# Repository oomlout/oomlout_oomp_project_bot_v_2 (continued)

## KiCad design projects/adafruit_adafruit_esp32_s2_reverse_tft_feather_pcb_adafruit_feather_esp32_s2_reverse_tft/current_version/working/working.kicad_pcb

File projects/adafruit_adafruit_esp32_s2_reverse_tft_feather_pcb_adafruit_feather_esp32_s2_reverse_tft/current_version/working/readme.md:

# adafruit_esp32_s2_reverse_tft_feather_pcb
 
## summary 
* id: adafruit_adafruit_esp32_s2_reverse_tft_feather_pcb_adafruit_feather_esp32_s2_reverse_tft
* user: adafruit
* name: adafruit_esp32_s2_reverse_tft_feather_pcb
* board: adafruit_feather_esp32_s2_reverse_tft
* repo: https://github.com/adafruit/Adafruit-ESP32-S2-Reverse-TFT-Feather-PCB

* src_file_repo_sch: 
* src_file_repo_sch_link: https://github.com/adafruit/Adafruit-ESP32-S2-Reverse-TFT-Feather-PCB/tree/main/
* full details link: https://github.com/oomlout/oomlout_oomp_project_bot_v_2/tree/main/projects/adafruit_adafruit_esp32_s2_reverse_tft_feather_pcb_adafruit_feather_esp32_s2_reverse_tft/current_version/working  

## schematic  
  
[schematic (pdf)](working_schematic.pdf) 

## pcb  

[board (pdf)](working.pdf)  

## working_bom
| Id | Designator | Footprint | Quantity | Designation | Supplier and ref |  | None | 
| --- | --- | --- | --- | --- | --- | --- | --- | 
| 1 | PLABEL17 | PLABEL17 | 1 |  |  |  | [''] | 
| 2 | R10,R4,R8,R2,R5 | 0603-NO | 5 | 5.1K |  |  | [''] | 
| 3 | C4,C5,C10,C11 | 0603-NO | 4 | 1uF |  |  | [''] | 
| 4 | C6,C8,C9,C1,C7,C3,C12,C2 | 0805-NO | 8 | 10uF |  |  | [''] | 
| 5 | PLABEL12 | PLABEL12 | 1 |  |  |  | [''] | 
| 6 | PLABEL16 | PLABEL16 | 1 |  |  |  | [''] | 
| 7 | PLABEL9 | PLABEL9 | 1 |  |  |  | [''] | 
| 8 | PLABEL0 | PLABEL0 | 1 |  |  |  | [''] | 
| 9 | PLABEL20 | PLABEL20 | 1 |  |  |  | [''] | 
| 10 | X2 | TDFN8_2X2MM | 1 | MAX17048/T |  |  | [''] | 
| 11 | PLABEL24 | PLABEL24 | 1 |  |  |  | [''] | 
| 12 | PLABEL15 | PLABEL15 | 1 |  |  |  | [''] | 
| 13 | U$35,U$34 | FIDUCIAL_1MM | 2 | FIDUCIAL_1MM |  |  | [''] | 
| 14 | PLABEL21 | PLABEL21 | 1 |  |  |  | [''] | 
| 15 | R17 | 0603-NO | 1 | 1Meg |  |  | [''] | 
| 16 | R13 | RESPACK_4X0603 | 1 | 10K Pack |  |  | [''] | 
| 17 | PLABEL28 | PLABEL28 | 1 |  |  |  | [''] | 
| 18 | PLABEL5 | PLABEL5 | 1 |  |  |  | [''] | 
| 19 | PLABEL1 | PLABEL1 | 1 |  |  |  | [''] | 
| 20 | U4 | BME280 | 1 | BME280 |  |  | [''] | 
| 21 | @HOLE1,@HOLE0 |  | 2 |  |  |  | [''] | 
| 22 | PLABEL18 | PLABEL18 | 1 |  |  |  | [''] | 
| 23 | PLABEL25 | PLABEL25 | 1 |  |  |  | [''] | 
| 24 | PLABEL6 | PLABEL6 | 1 |  |  |  | [''] | 
| 25 | U5,U2 | SOT23-5 | 2 | RT9080/AP2112-3.3 |  |  | [''] | 
| 26 | PLABEL14 | PLABEL14 | 1 |  |  |  | [''] | 
| 27 | X1 | JSTPH2_BATT | 1 | JSTPH |  |  | [''] | 
| 28 | D3 | CHIPLED_0603_NOOUTLINE | 1 | RED |  |  | [''] | 
| 29 | JP1 | 1X16_ROUND_MIN | 1 |  |  |  | [''] | 
| 30 | CHG0 | CHIPLED_0603_NOOUTLINE | 1 | ORANGE |  |  | [''] | 
| 31 | PLABEL2 | PLABEL2 | 1 |  |  |  | [''] | 
| 32 | Q3 | SOT23-R | 1 | DMG3415U |  |  | [''] | 
| 33 | PLABEL4 | PLABEL4 | 1 |  |  |  | [''] | 
| 34 | PLABEL13 | PLABEL13 | 1 |  |  |  | [''] | 
| 35 | PLABEL31 | PLABEL31 | 1 |  |  |  | [''] | 
| 36 | U3 | SOT23-5 | 1 | MCP73831T-2ACI/OT |  |  | [''] | 
| 37 | R9 | 0603-NO | 1 | 22ohm |  |  | [''] | 
| 38 | PLABEL30 | PLABEL30 | 1 |  |  |  | [''] | 
| 39 | D4 | SOD-123 | 1 | MBR540 |  |  | [''] | 
| 40 | PLABEL19 | PLABEL19 | 1 |  |  |  | [''] | 
| 41 | PLABEL27 | PLABEL27 | 1 |  |  |  | [''] | 
| 42 | PLABEL8 | PLABEL8 | 1 |  |  |  | [''] | 
| 43 | JP3 | 1X12_ROUND_MIN | 1 |  |  |  | [''] | 
| 44 | Q1 | SC70 | 1 | BSS138 |  |  | [''] | 
| 45 | X3 | USB_C_CUSB31-CFM2AX-01-X | 1 | USB C |  |  | [''] | 
| 46 | R1 | 0603-NO | 1 | 10K |  |  | [''] | 
| 47 | SW2,SW5,SW3,SW1,SW4 | BTN_RKB2_4.6X2.8 | 5 | KMR2 |  |  | [''] | 
| 48 | R12,R7 | 0603-NO | 2 | 100K |  |  | [''] | 
| 49 | PLABEL11 | PLABEL11 | 1 |  |  |  | [''] | 
| 50 | PLABEL26 | PLABEL26 | 1 |  |  |  | [''] | 
| 51 | PLABEL29 | PLABEL29 | 1 |  |  |  | [''] | 
| 52 | PLABEL3 | PLABEL3 | 1 |  |  |  | [''] | 
| 53 | PLABEL7 | PLABEL7 | 1 |  |  |  | [''] | 
| 54 | PLABEL22 | PLABEL22 | 1 |  |  |  | [''] | 
| 55 | U$32,U$31 | MOUNTINGHOLE_2.5_PLATED | 2 | MOUNTINGHOLE2.5 |  |  | [''] | 
| 56 | LED1 | SK6805_1515 | 1 | WS2812B_SK6805_1515 |  |  | [''] | 
| 57 | CONN1 | JST_SH4_RA | 1 | STEMMA_I2C_QTRA |  |  | [''] | 
| 58 | PLABEL23 | PLABEL23 | 1 |  |  |  | [''] | 
| 59 | PLABEL10 | PLABEL10 | 1 |  |  |  | [''] | 
| 60 | U1 | ESP32-S2-MINI-1 | 1 | ESP32-S2-MODULE_MINI |  |  | [''] | 
| 61 | PLABEL32 | PLABEL32 | 1 |  |  |  | [''] | 
| 62 | PLABEL33 | PLABEL33 | 1 |  |  |  | [''] | 
| 63 | PLABEL35 | PLABEL35 | 1 |  |  |  | [''] | 
| 64 | PLABEL34 | PLABEL34 | 1 |  |  |  | [''] | 
| 65 | PLABEL36 | PLABEL36 | 1 |  |  |  | [''] | 
| 66 | DISP1 | TFT_1.14IN_240X135_WRAPUNDER | 1 | DISP_LCD_GENERIC_SPI_1.14IN_240X135_WRAPUNDER |  |  | [''] | 
| 67 | TP1 | TESTPOINT_ROUND_1.5MM_NO | 1 |  |  |  | [''] | 

## bom_schematic
| Ref | Qnty | Value | Cmp name | Footprint | Description | Vendor | DNP | 
| --- | --- | --- | --- | --- | --- | --- | --- | 
| C1, C2, C3, C6, C7, C8, C9, C12 | 8 | 10uF | CAP_CERAMIC0805-NOOUTLINE | working:0805-NO |  |  |  | 
| C4, C5, C10, C11 | 4 | 1uF | CAP_CERAMIC0603_NO | working:0603-NO |  |  |  | 
| CHG0 | 1 | ORANGE | LED0603_NOOUTLINE | working:CHIPLED_0603_NOOUTLINE |  |  |  | 
| CONN1 | 1 | STEMMA_I2C_QTRA | STEMMA_I2C_QTRA | working:JST_SH4_RA |  |  |  | 
| D3 | 1 | RED | LED0603_NOOUTLINE | working:CHIPLED_0603_NOOUTLINE |  |  |  | 
| D4 | 1 | MBR540 | DIODE-SCHOTTKYSOD-123 | working:SOD-123 |  |  |  | 
| DISP1 | 1 | DISP_LCD_GENERIC_SPI_1.14IN_240X135_WRAPUNDER | DISP_LCD_GENERIC_SPI_1.14IN_240X135_WRAPUNDER | working:TFT_1.14IN_240X135_WRAPUNDER |  |  |  | 
| JP1 | 1 | HEADER-1X16_MIN | HEADER-1X16_MIN | working:1X16_ROUND_MIN |  |  |  | 
| JP3 | 1 | HEADER-1X12_MIN | HEADER-1X12_MIN | working:1X12_ROUND_MIN |  |  |  | 
| LED1 | 1 | WS2812B_SK6805_1515 | WS2812B_SK6805_1515 | working:SK6805_1515 |  |  |  | 
| Q1 | 1 | BSS138 | MOSFET-N_SC70 | working:SC70 |  |  |  | 
| Q3 | 1 | DMG3415U | MOSFET-P | working:SOT23-R |  |  |  | 
| R1 | 1 | 10K | RESISTOR_0603_NOOUT | working:0603-NO |  |  |  | 
| R2, R4, R5, R8, R10 | 5 | 5.1K | RESISTOR_0603_NOOUT | working:0603-NO |  |  |  | 
| R7, R12 | 2 | 100K | RESISTOR_0603_NOOUT | working:0603-NO |  |  |  | 
| R9 | 1 | 22ohm | RESISTOR_0603_NOOUT | working:0603-NO |  |  |  | 
| R13 | 1 | 10K Pack | RESISTOR_4PACK | working:RESPACK_4X0603 |  |  |  | 
| R17 | 1 | 1Meg | RESISTOR_0603_NOOUT | working:0603-NO |  |  |  | 
| SW1, SW2, SW3, SW4, SW5 | 5 | KMR2 | SWITCH_TACT_SMT_RKB2 | working:BTN_RKB2_4.6X2.8 |  |  |  | 
| TP1 | 1 | TESTPOINTROUND1.5MMNO | TESTPOINTROUND1.5MMNO | working:TESTPOINT_ROUND_1.5MM_NO |  |  |  | 
| U1 | 1 | ESP32-S2-MODULE_MINI | ESP32-S2-MODULE_MINI | working:ESP32-S2-MINI-1 |  |  |  | 
| U2, U5 | 2 | RT9080/AP2112-3.3 | VREG_SOT23-5 | working:SOT23-5 |  |  |  | 
| U3 | 1 | MCP73831T-2ACI/OT | MCP73831/2 | working:SOT23-5 |  |  |  | 
| U4 | 1 | BME280 | BME280 | working:BME280 |  |  |  | 
| U$31, U$32 | 2 | MOUNTINGHOLE2.5 | MOUNTINGHOLE2.5 | working:MOUNTINGHOLE_2.5_PLATED |  |  |  | 
| U$34, U$35 | 2 | FIDUCIAL_1MM | FIDUCIAL_1MM | working:FIDUCIAL_1MM |  |  |  | 
| X1 | 1 | CON_JST_PH_2PIN_MT_BATT | CON_JST_PH_2PIN_MT_BATT | working:JSTPH2_BATT |  |  |  | 
| X2 | 1 | MAX17048/T | MAX17048/T | working:TDFN8_2X2MM |  |  |  | 
| X3 | 1 | USB C | USB_C | working:USB_C_CUSB31-CFM2AX-01-X |  |  |  | 

## mounting_holes
| x | y | package | value | ref | size | 
| --- | --- | --- | --- | --- | --- | 
| 0.0 | 17.78 | MOUNTINGHOLE_2.5_PLATED | MOUNTINGHOLE2.5 | U$31 | m3 | 
| 0.0 | 0.0 | MOUNTINGHOLE_2.5_PLATED | MOUNTINGHOLE2.5 | U$32 | m3 |

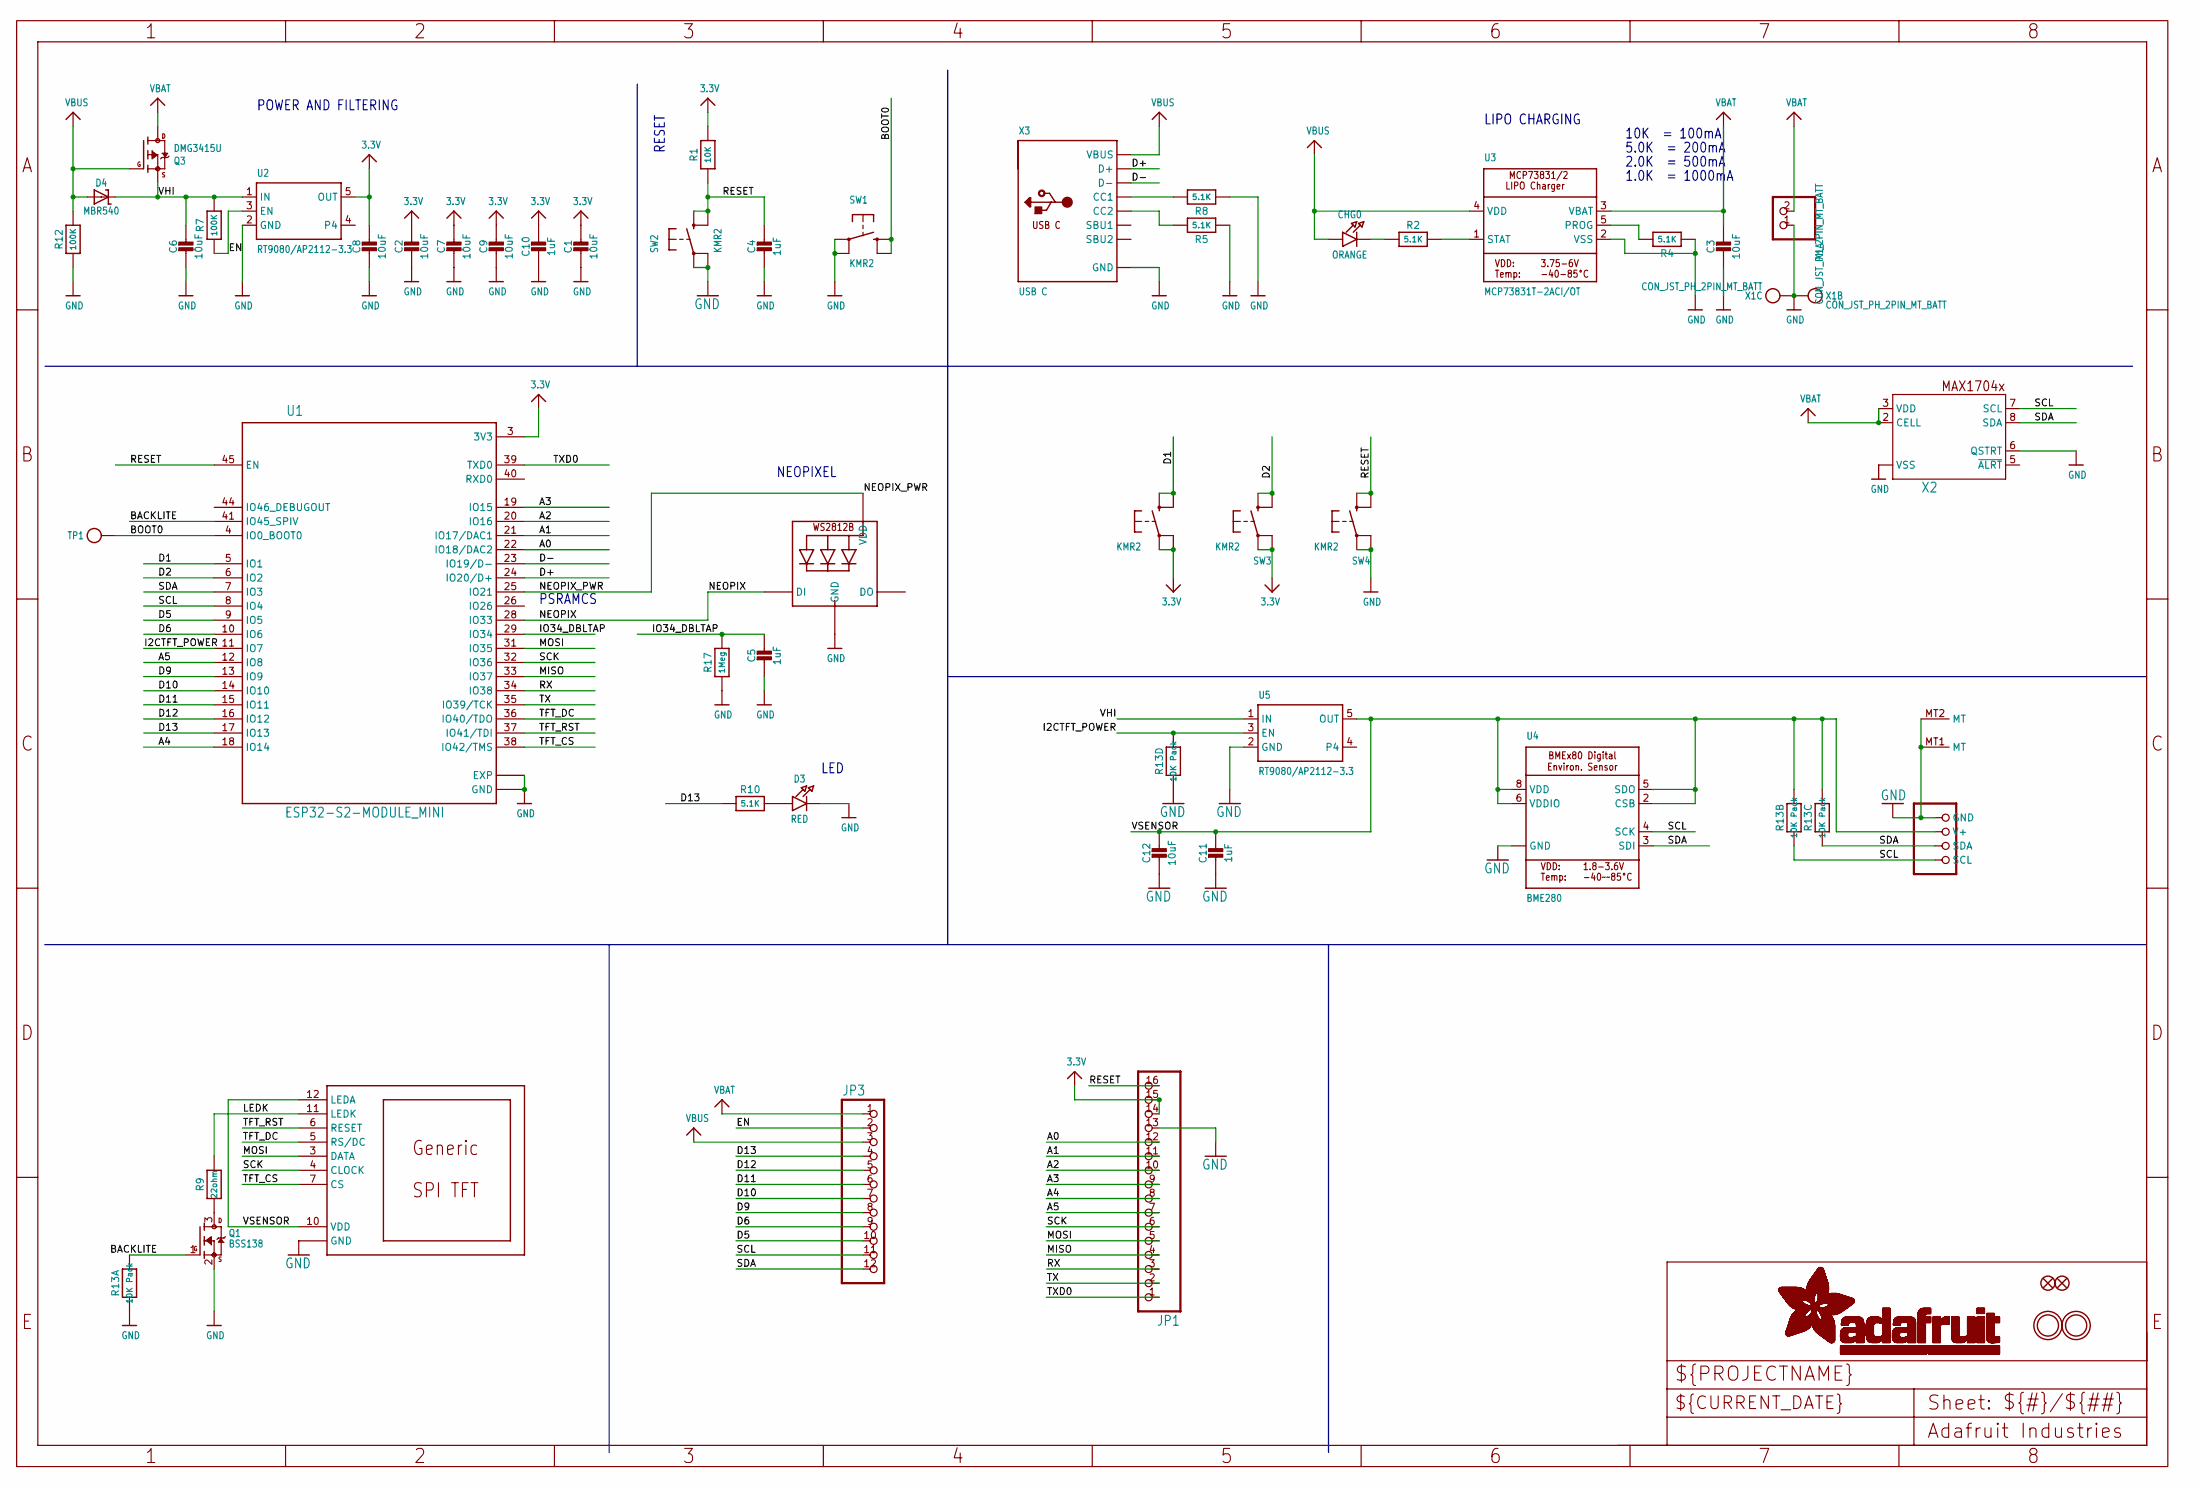
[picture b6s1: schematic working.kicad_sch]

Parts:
C1, C2, C3, C6, C7, C8, C9, C12: 10uF; 0805-NO
C4, C5, C10, C11: 1uF; 0603-NO
CHG0: ORANGE; CHIPLED_0603_NOOUTLINE
CONN1: STEMMA_I2C_QTRA; JST_SH4_RA
D3: RED; CHIPLED_0603_NOOUTLINE
D4: MBR540; SOD-123
DISP1: DISP_LCD_GENERIC_SPI_1.14IN_240X135_WRAPUNDER; TFT_1.14IN_240X135_WRAPUNDER
JP1: HEADER-1X16_MIN; 1X16_ROUND_MIN
JP3: HEADER-1X12_MIN; 1X12_ROUND_MIN
LED1: WS2812B_SK6805_1515; SK6805_1515
Q1: BSS138; SC70
Q3: DMG3415U; SOT23-R
R1: 10K; 0603-NO
R2, R4, R5, R8, R10: 5.1K; 0603-NO
R7, R12: 100K; 0603-NO
R9: 22ohm; 0603-NO
R13: 10K Pack; RESPACK_4X0603
R17: 1Meg; 0603-NO
SW1, SW2, SW3, SW4, SW5: KMR2; BTN_RKB2_4.6X2.8
TP1: TESTPOINTROUND1.5MMNO; TESTPOINT_ROUND_1.5MM_NO
U1: ESP32-S2-MODULE_MINI; ESP32-S2-MINI-1
U2, U5: RT9080/AP2112-3.3; SOT23-5; JLC_ROTATION 0
U3: MCP73831T-2ACI/OT; SOT23-5
U4: BME280
U$31, U$32: MOUNTINGHOLE2.5; MOUNTINGHOLE_2.5_PLATED
U$34, U$35: FIDUCIAL_1MM
X1: CON_JST_PH_2PIN_MT_BATT; JSTPH2_BATT
X2: MAX17048/T; TDFN8_2X2MM
X3: USB C; USB_C_CUSB31-CFM2AX-01-X

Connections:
3.3V: C1.1, C2.1, C7.1, C8.1, C9.1, C10.1, JP1.14, JP1.15, R1.2, SW3.A, SW3.A' (P1), SW5.A, SW5.A' (P1), U1.3 (3V3), U2.5 (OUT)
A0: JP1.12, U1.22 (IO18/DAC2)
A1: JP1.11, U1.21 (IO17/DAC1)
A2: JP1.10, U1.20 (IO16)
A3: JP1.9, U1.19 (IO15)
A4: JP1.8, U1.18 (IO14)
A5: JP1.7, U1.12 (IO8)
BACKLITE: Q1.1 (G), R13.8 (2), U1.41 (IO45_SPIV)
BOOT0: SW1.B (S), SW1.B' (S1), TP1.P$1, U1.4 (IO0_BOOT0)
D1: SW5.B (S), SW5.B' (S1), U1.5 (IO1)
D2: SW3.B (S), SW3.B' (S1), U1.6 (IO2)
D5: JP3.10, U1.9 (IO5)
D6: JP3.9, U1.10 (IO6)
D9: JP3.8, U1.13 (IO9)
D10: JP3.7, U1.14 (IO10)
D11: JP3.6, U1.15 (IO11)
D12: JP3.5, U1.16 (IO12)
D13: JP3.4, R10.1, U1.17 (IO13)
D+: U1.24 (IO20/D+), X3.A6 (D+), X3.B6 (D+)
D-: U1.23 (IO19/D-), X3.A7 (D-), X3.B7 (D-)
EN: JP3.2, R7.1, U2.3 (EN)
GND: C1.2, C2.2, C3.2, C4.2, C5.2, C6.2, C7.2, C8.2, C9.2, C10.2, C11.2, C12.2, CONN1.1 (GND), CONN1.MT1 (MT), CONN1.MT2 (MT), D3.C, DISP1.8 (GND), DISP1.13 (GND), JP1.13, LED1.4 (GND), Q1.2 (S), R4.1, R5.1, R8.1, R12.1, R13.1, R13.4 (1), R17.1, SW1.A, SW1.A' (P1), SW2.A, SW2.A' (P1), SW4.A, SW4.A' (P1), U1.1 (GND), U1.2 (GND), U1.30 (GND), U1.42 (GND), U1.43 (GND), U1.46 (GND), U1.47 (GND), U1.48 (GND), U1.49 (GND), U1.50 (GND), U1.51 (GND), U1.52 (GND), U1.53 (GND), U1.54 (GND), U1.55 (GND), U1.56 (GND), U1.57 (GND), U1.58 (GND), U1.59 (GND), U1.60 (GND), U1.61 (EXP), U1.62 (EXP), U1.63 (EXP), U1.64 (EXP), U1.65 (EXP), U1.66 (EXP), U1.67 (EXP), U1.68 (EXP), U1.69 (EXP), U1.70 (EXP), U1.71 (EXP), U1.72 (EXP), U1.73 (EXP), U2.2 (GND), U3.2 (VSS), U4.1 (GND), U4.7 (GND), U5.2 (GND), X1.1, X1.NC1, X1.NC2, X2.1 (VSS), X2.4 (VSS), X2.6 (QSTRT), X2.THERMAL (VSS), X3.A1B12 (GND), X3.B1A12 (GND)
I2CTFT_POWER: R13.5 (2), U1.11 (IO7), U5.3 (EN)
IO34_DBLTAP: C5.1, R17.2, U1.29 (IO34)
LEDK: DISP1.11 (LEDK), R9.2
MISO: JP1.4, U1.33 (IO37)
MOSI: DISP1.3 (DATA), JP1.5, U1.31 (IO35)
unnamed: CHG0.C, R2.1
unnamed: Q1.3 (D), R9.1
unnamed: R2.2, U3.1 (STAT)
unnamed: R4.2, U3.5 (PROG)
unnamed: D3.A, R10.2
unnamed: R8.2, X3.A5 (CC1)
unnamed: R5.2, X3.B5 (CC2)
NEOPIX: LED1.1 (DI), U1.28 (IO33)
NEOPIX_PWR: LED1.2 (VDD), U1.25 (IO21)
RESET: C4.1, JP1.16, R1.1, SW2.B (S), SW2.B' (S1), SW4.B (S), SW4.B' (S1), U1.45 (EN)
RX: JP1.3, U1.34 (IO38)
SCK: DISP1.4 (CLOCK), JP1.6, U1.32 (IO36)
SCL: CONN1.4 (SCL), JP3.11, R13.2 (1), U1.8 (IO4), U4.4 (SCK), X2.7 (SCL)
SDA: CONN1.3 (SDA), JP3.12, R13.3 (1), U1.7 (IO3), U4.3 (SDI), X2.8 (SDA)
TFT_CS: DISP1.7 (CS), U1.38 (IO42/TMS)
TFT_DC: DISP1.5 (RS/DC), U1.36 (IO40/TDO)
TFT_RST: DISP1.6 (RESET), U1.37 (IO41/TDI)
TX: JP1.2, U1.35 (IO39/TCK)
TXD0: JP1.1, U1.39 (TXD0)
VBAT: C3.1, JP3.1, Q3.3 (D), U3.3 (VBAT), X1.2, X2.2 (CELL), X2.3 (VDD)
VBUS: CHG0.A, D4.A, JP3.3, Q3.1 (G), R12.2, U3.4 (VDD), X3.A4B9 (VBUS), X3.B4A9 (VBUS)
VHI: C6.1, D4.C, Q3.2 (S), R7.2, U2.1 (IN), U5.1 (IN)
VSENSOR: C11.1, C12.1, CONN1.2 (V+), DISP1.10 (VDD), DISP1.12 (LEDA), R13.6 (2), R13.7 (2), U4.2 (CSB), U4.5 (SDO), U4.6 (VDDIO), U4.8 (VDD), U5.5 (OUT)

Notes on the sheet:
LIPO CHARGING
POWER AND FILTERING
LED
PSRAMCS
RESET
NEOPIXEL
10K = 100mA
1.0K = 1000mA
5.0K = 200mA
2.0K = 500mA

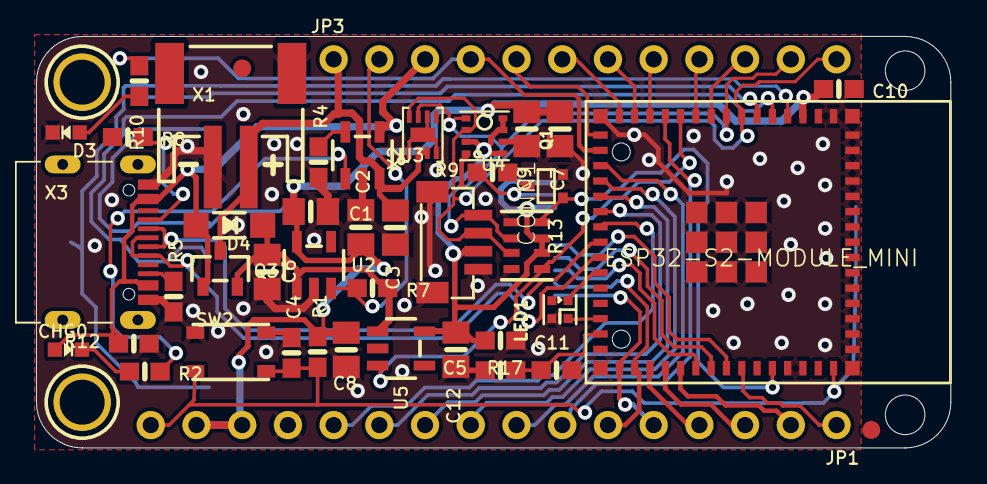
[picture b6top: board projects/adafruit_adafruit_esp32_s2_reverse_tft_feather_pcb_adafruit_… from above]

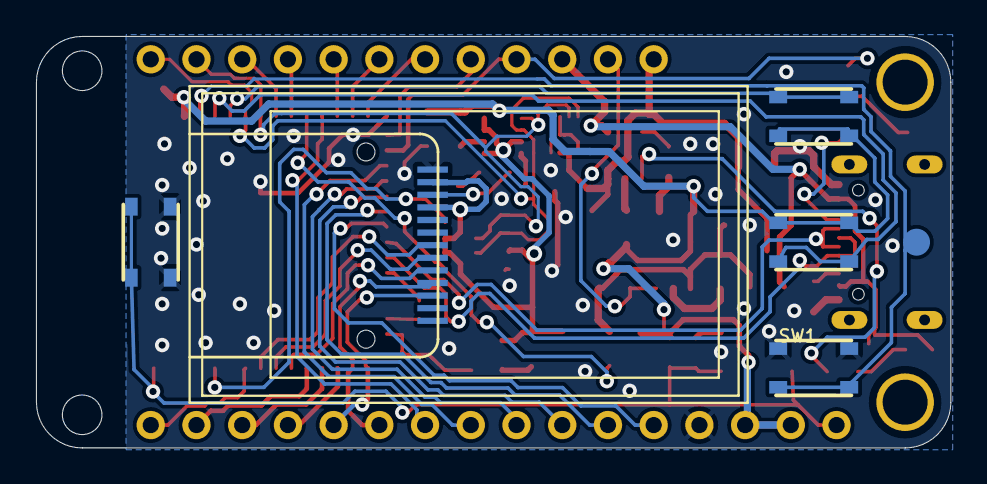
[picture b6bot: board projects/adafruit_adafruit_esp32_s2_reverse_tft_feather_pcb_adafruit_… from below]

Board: 2 copper layers, 50.8 x 22.9 mm, 90 parts (11 on the bottom side), 50 nets.

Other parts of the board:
@HOLE0, @HOLE1: (no value)
PLABEL0: PLABEL0
PLABEL1: PLABEL1
PLABEL2: PLABEL2
PLABEL3: PLABEL3
PLABEL4: PLABEL4
PLABEL5: PLABEL5
PLABEL6: PLABEL6
PLABEL7: PLABEL7
PLABEL8: PLABEL8
PLABEL9: PLABEL9
PLABEL10: PLABEL10
PLABEL11: PLABEL11
PLABEL12: PLABEL12
PLABEL13: PLABEL13
PLABEL14: PLABEL14
PLABEL15: PLABEL15
PLABEL16: PLABEL16
PLABEL17: PLABEL17
PLABEL18: PLABEL18
PLABEL19: PLABEL19
PLABEL20: PLABEL20
PLABEL21: PLABEL21
PLABEL22: PLABEL22
PLABEL23: PLABEL23
PLABEL24: PLABEL24
PLABEL25: PLABEL25
PLABEL26: PLABEL26
PLABEL27: PLABEL27
PLABEL28: PLABEL28
PLABEL29: PLABEL29
PLABEL30: PLABEL30
PLABEL31: PLABEL31
PLABEL32: PLABEL32
PLABEL33: PLABEL33
PLABEL34: PLABEL34
PLABEL35: PLABEL35
PLABEL36: PLABEL36
